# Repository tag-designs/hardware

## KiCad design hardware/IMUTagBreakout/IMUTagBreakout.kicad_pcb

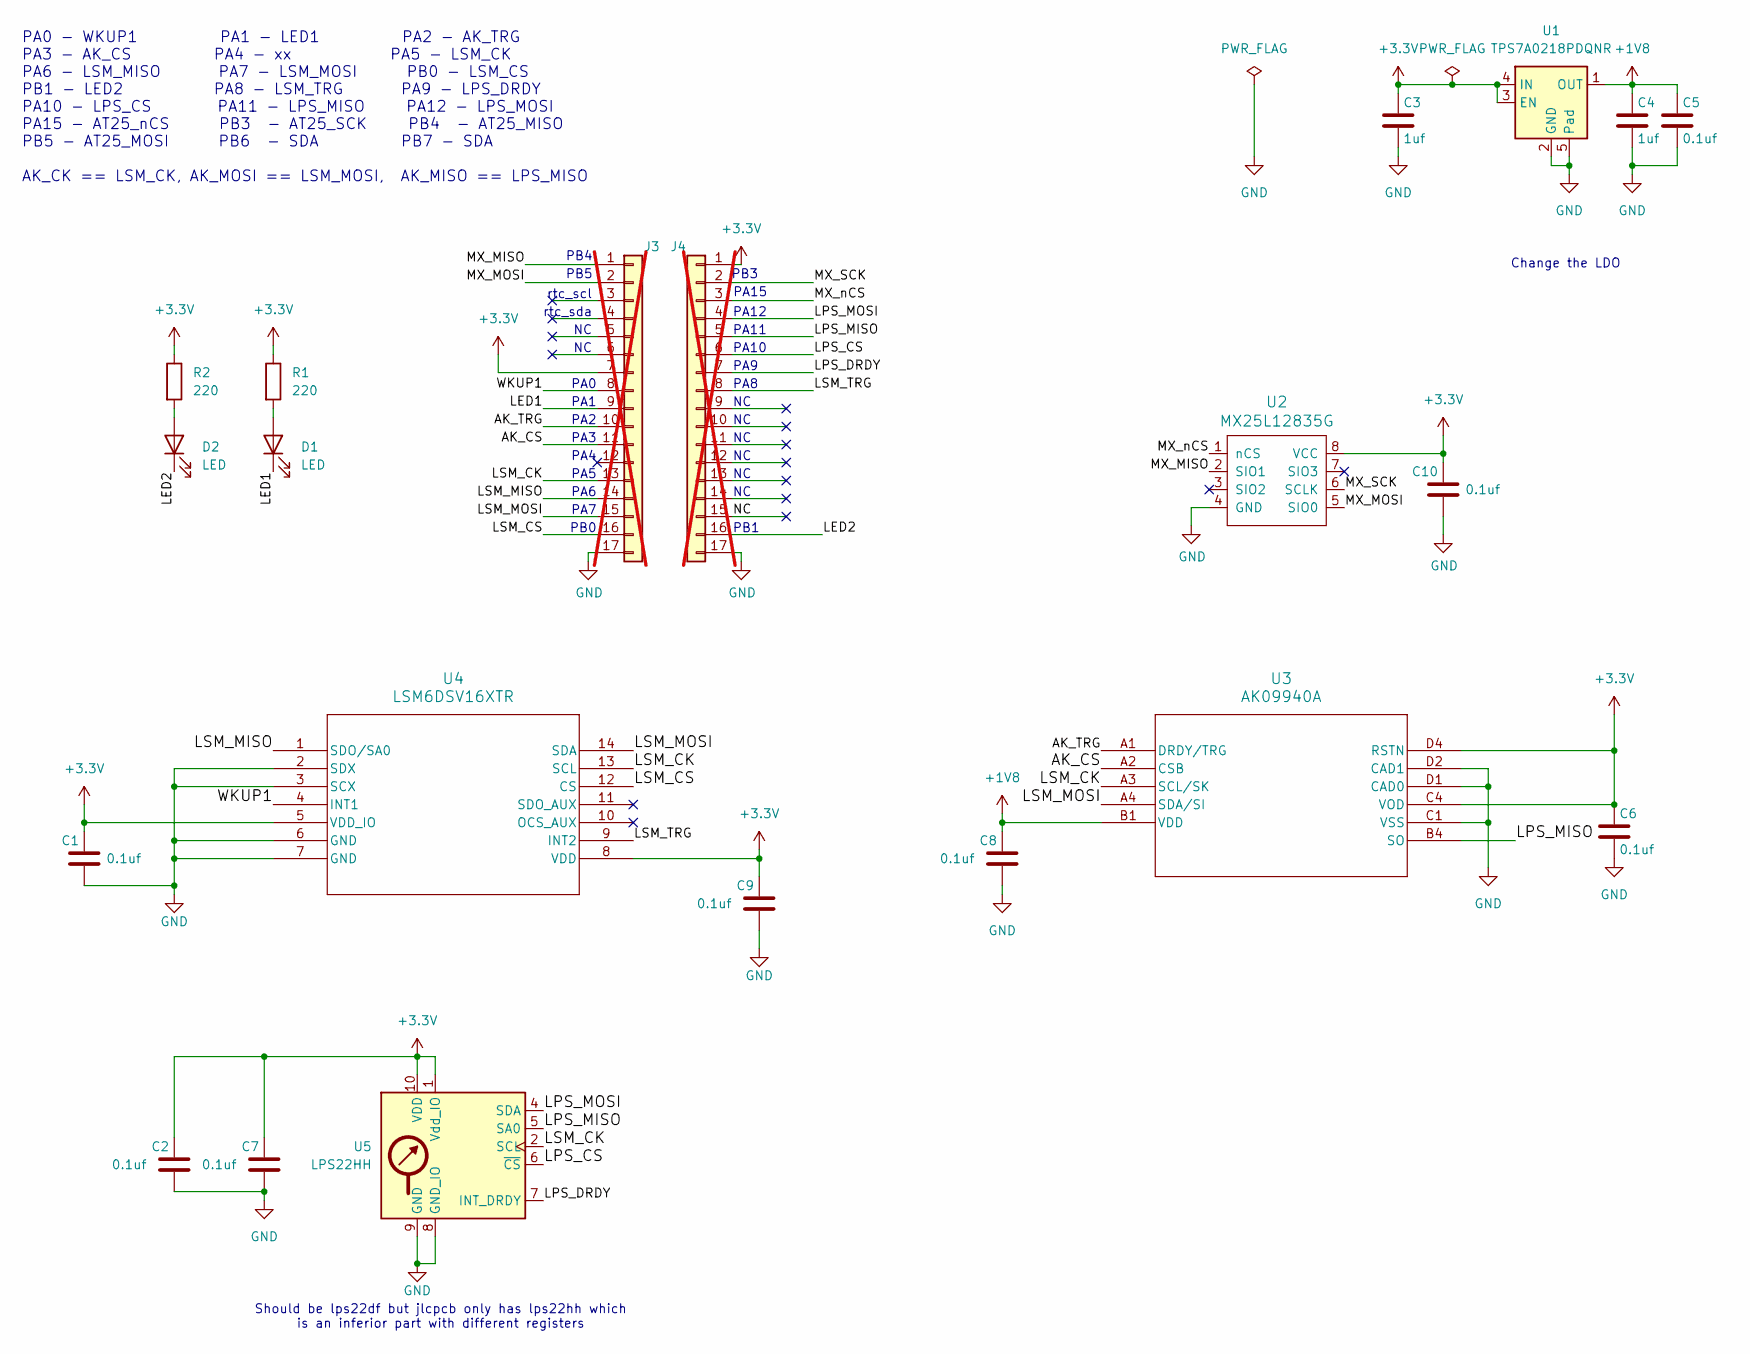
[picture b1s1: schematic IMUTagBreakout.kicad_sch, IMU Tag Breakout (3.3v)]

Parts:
C1, C2, C5, C6, C7, C8, C9, C10: 0.1uf; C_0603_1608Metric; MPN CC0603KRX7R9BB104; LCSC C14663
C3, C4: 1uf; C_0603_1608Metric; MPN CL10A105KB8NNNC; LCSC C15849
D1, D2: LED; LED_0603_1608Metric; MPN KT-0603R; LCSC C2286
J3, J4: Conn_01x17; PinHeader_1x17_P2.54mm_Vertical_Staggered; not fitted
R1, R2: 220; R_0603_1608Metric; MPN 0603WAF2200T5E; LCSC C22962
U1: TPS7A0218PDQNR; Texas_X2SON-4_1x1mm_P0.65mm; MPN TPS7A0218PDQNR; LCSC C2862166
U2: MX25L12835G; SOIC-8_5.3x6.2mm_P1.27mm; MPN MX25L12845GM2I-08G-TR; LCSC C136615
U3: AK09940A; AK09940a; MPN AK09940A; LCSC C6794828
U4: LSM6DSV16XTR; LGA-14_3x2.5mm_P0.5mm_LayoutBorder3x4y; MPN LSM6DSV; LCSC C5267406
U5: LPS22HH; ST_HLGA-10_2x2mm_P0.5mm_LayoutBorder3x2y; MPN LPS22HH; LCSC C2827824

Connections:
+1V8: C4.1, C5.1, C8.1, U1.1 (OUT), U3.B1 (VDD)
+3.3V: C1.1, C2.1, C3.1, C6.1, C7.1, C9.1, C10.1, J3.7, J4.1, R1.1, R2.1, U1.3 (EN), U1.4 (IN), U2.8 (VCC), U3.C4 (VOD), U3.D4 (RSTN), U4.5 (VDD_IO), U4.8 (VDD), U5.1 (Vdd_IO), U5.10 (VDD)
/AK_CS: J3.11, U3.A2 (CSB)
/AK_TRG: J3.10, U3.A1 (DRDY/TRG)
/LED1: D1.1 (K), J3.9
/LED2: D2.1 (K), J4.16
/LPS_CS: J4.6, U5.6 (~CS)
/LPS_DRDY: J4.7, U5.7 (INT_DRDY)
/LPS_MISO: J4.5, U3.B4 (SO), U5.5 (SA0)
/LPS_MOSI: J4.4, U5.4 (SDA)
/LSM_CK: J3.13, U3.A3 (SCL/SK), U4.13 (SCL), U5.2 (SCL)
/LSM_CS: J3.16, U4.12 (CS)
/LSM_MISO: J3.14, U4.1 (SDO/SA0)
/LSM_MOSI: J3.15, U3.A4 (SDA/SI), U4.14 (SDA)
/LSM_TRG: J4.8, U4.9 (INT2)
/MX_MISO: J3.1, U2.2 (SIO1)
/MX_MOSI: J3.2, U2.5 (SIO0)
/MX_SCK: J4.2, U2.6 (SCLK)
/MX_nCS: J4.3, U2.1 (nCS)
/NC: J4.15
/WKUP1: J3.8, U4.4 (INT1)
GND: C1.2, C2.2, C3.2, C4.2, C5.2, C6.2, C7.2, C8.2, C9.2, C10.2, J3.17, J4.17, U1.2 (GND), U1.5 (Pad), U2.4 (GND), U3.C1 (VSS), U3.D1 (CAD0), U3.D2 (CAD1), U4.2 (SDX), U4.3 (SCX), U4.6 (GND), U4.7 (GND), U5.3 (GND), U5.8 (GND_IO), U5.9 (GND)
unnamed: D1.2 (A), R1.2
unnamed: D2.2 (A), R2.2

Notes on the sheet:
PA1
PA9
PA2
PA0
PA8
PA7
PA15
PA5
PA4
PB3
PA6
Should be lps22df but jlcpcb only has lps22hh which is an inferior part with different registers
PA3
PB4
PA12
PB0
PA0 - WKUP1 PA1 - LED1 PA2 - AK_TRG PA3 - AK_CS PA4 - xx PA5 - LSM_CK PA6 - LSM_MISO PA7 - LSM_MOSI PB0 - LSM_CS PB1 - LED2 PA8 - LSM_TRG PA9 - LPS_DRDY PA10 - LPS_CS PA11 - LPS_MISO PA12 - LPS_MOSI PA15 - AT25_nCS PB3 - AT25_SCK PB4 - AT25_MISO PB5 - AT25_MOSI PB6 - SDA PB7 - SDA AK_CK == LSM_CK, 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
PB5
PA10
rtc_sda
PA11
PB1
rtc_scl
Change the LDO

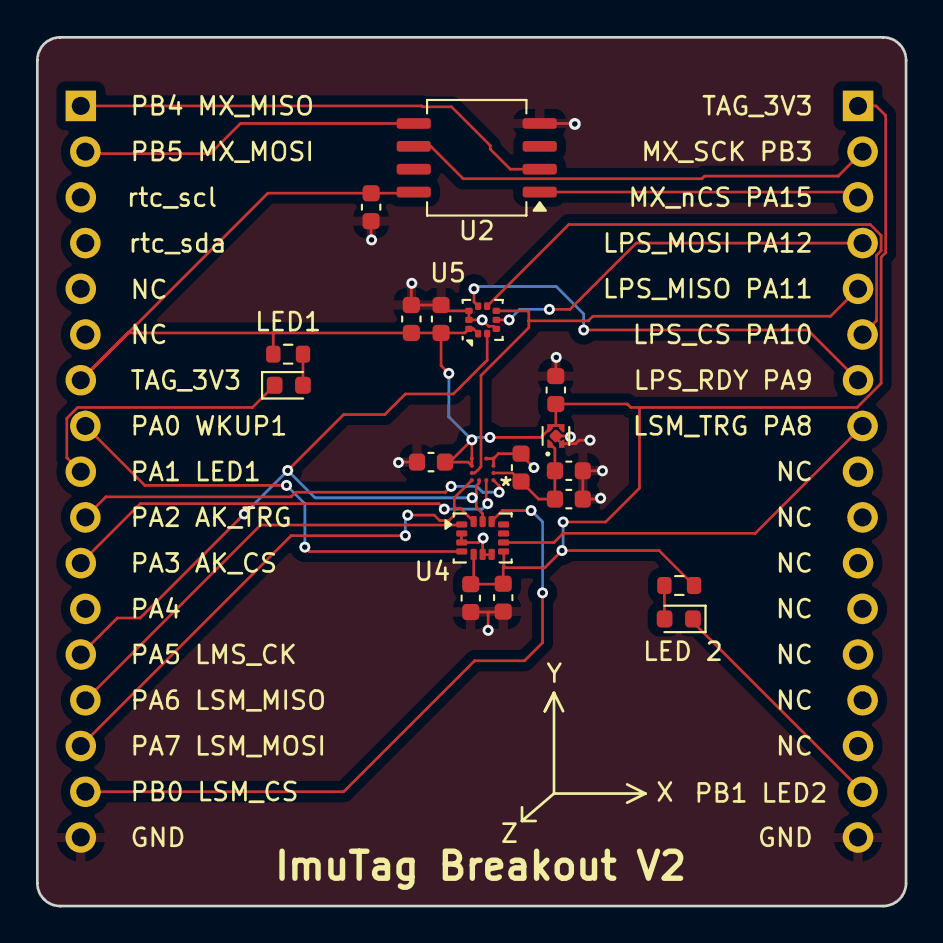
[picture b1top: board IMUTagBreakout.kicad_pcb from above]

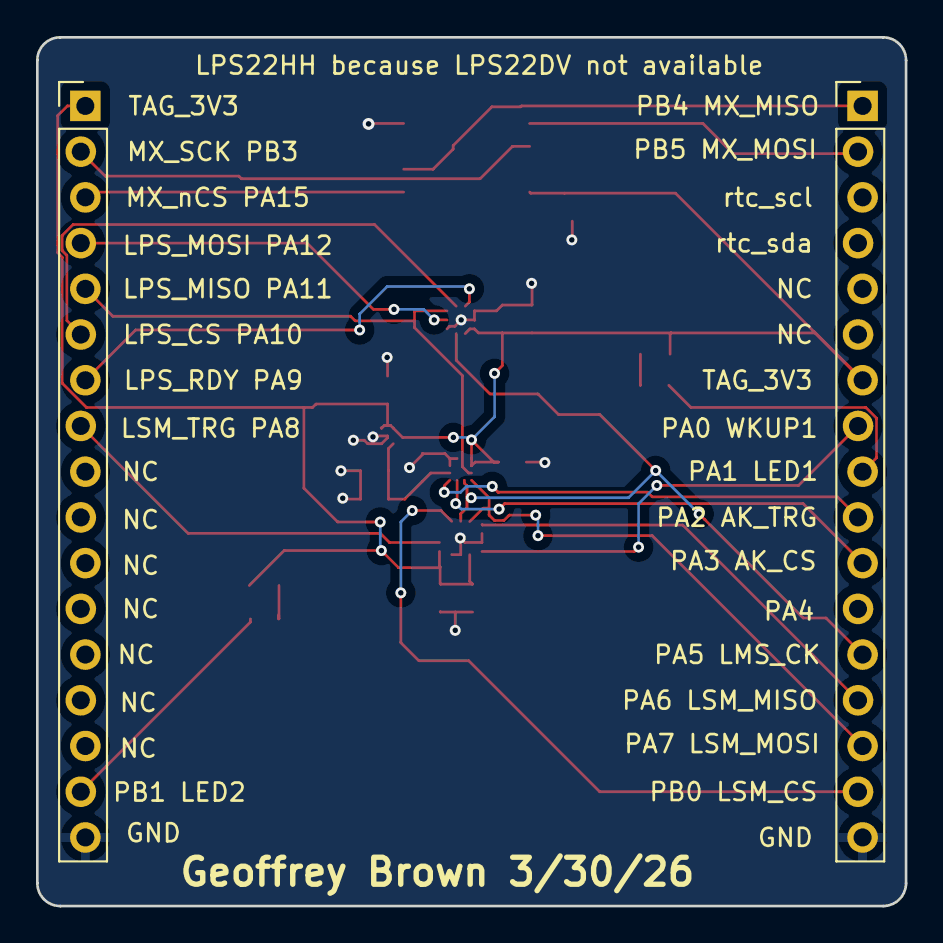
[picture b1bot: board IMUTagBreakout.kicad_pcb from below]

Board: 2 copper layers, 48.3 x 48.3 mm, 21 parts (2 on the bottom side), 23 nets.

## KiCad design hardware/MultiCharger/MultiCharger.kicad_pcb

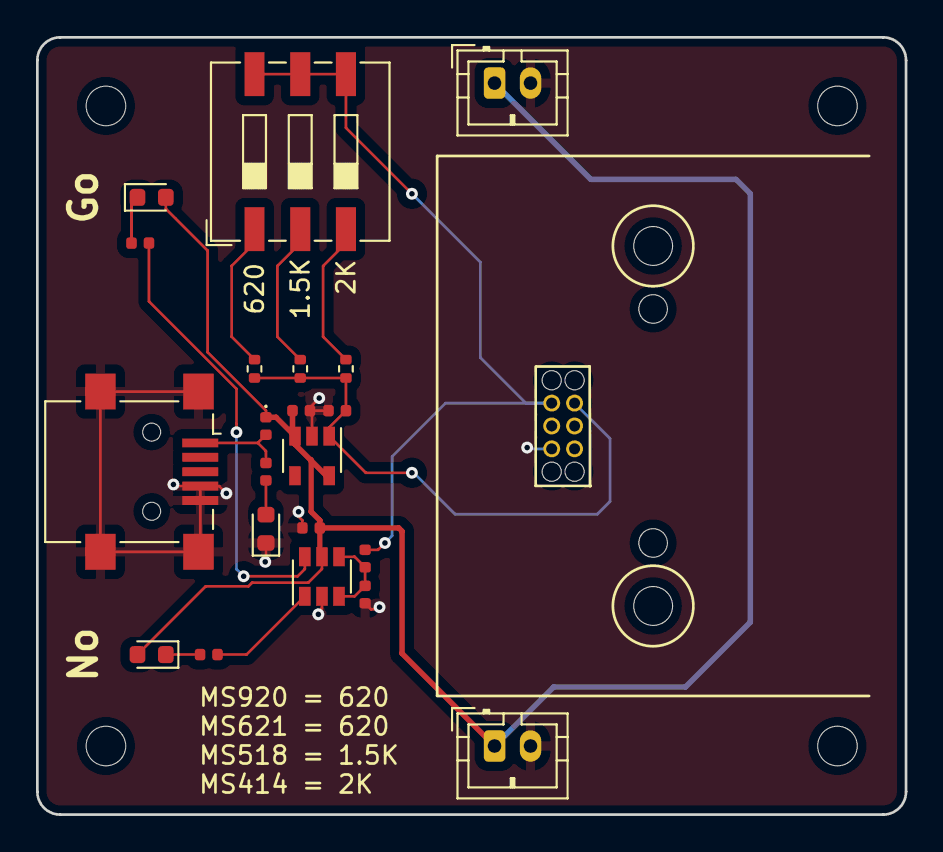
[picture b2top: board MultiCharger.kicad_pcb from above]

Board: 2 copper layers, 48.3 x 43.2 mm, 26 parts (0 on the bottom side), 14 nets.

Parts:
C101: 0.1uF; C_0402_1005Metric
C106: 1uF; C_0402_1005Metric
C107: 2.2uF; C_0402_1005Metric
D101: No Go; LED_0603_1608Metric
D102: LED; LED_0603_1608Metric
D103: Go; LED_0603_1608Metric
D104: D; D_0402_1005Metric
J101, J102: Conn_01x02; JST_PH_B2B-PH-K_1x02_P2.00mm_Vertical
J103: Tagbase; 6pin_tagpoints_new_offset
J104: USB_B_Mini; USB_Mini-B_Lumberg_2486_01_Horizontal
MK101, MK102, MK103, MK104: Mounting_Hole; MountingHole_2.2mm_M2
R1: 620; R_0402_1005Metric
R101, R102, R105: 1K; R_0402_1005Metric
R103: 910K; R_0402_1005Metric
R104: 130K; R_0402_1005Metric
R106: 1500; R_0402_1005Metric
R107: 2000; R_0402_1005Metric
SW101: SW_DIP_x03; SW_DIP_SPSTx03_Slide_9.78x9.8mm_W8.61mm_P2.54mm
U101: TLV6700; SOT-23-6
U106: TLV70A933_SOT23-5; SOT-23-5

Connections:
+3V3: C107.1, J103.5, R1.2, R106.2, R107.2, U106.1
/VIN: C101.1, C106.1, D101.2, D103.2, D104.1, J101.1, J102.1, U101.5, U106.3, U106.5
/Vsense: R103.2, R104.1, U101.3, U101.4
GND: C101.2, C106.2, C107.2, D102.1, J101.2, J102.2, J103.2, J104.4, J104.5, J104.6, R104.2, U101.2, U106.2
unnamed: D101.1, R101.2
unnamed: D102.2, R102.2
unnamed: D103.1, R105.2
unnamed: D104.2, J104.1, R102.1
unnamed: R1.1, SW101.1
unnamed: R101.1, U101.1
unnamed: R105.1, U101.6
unnamed: R106.1, SW101.2
unnamed: R107.1, SW101.3
TAG_VBAT: J103.6, R103.1, SW101.4, SW101.5, SW101.6

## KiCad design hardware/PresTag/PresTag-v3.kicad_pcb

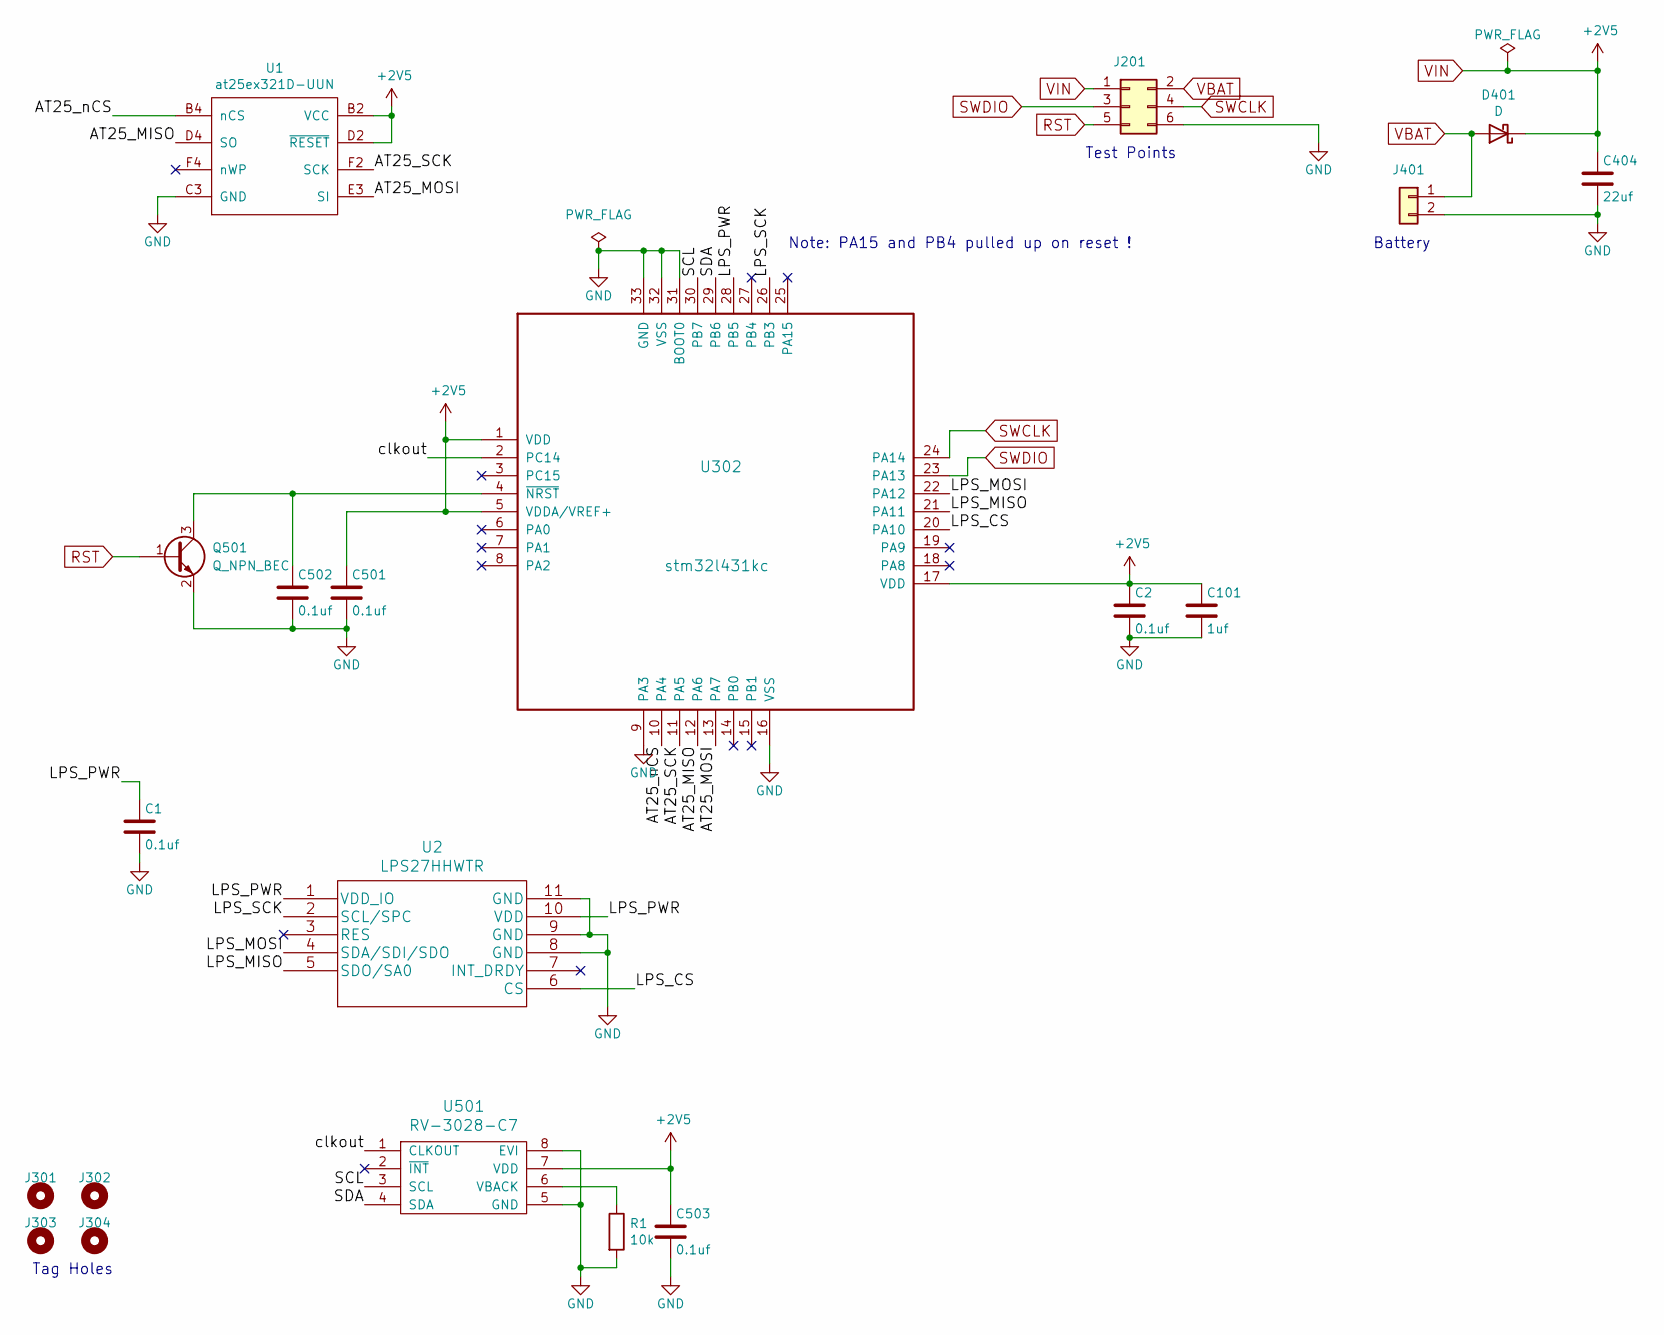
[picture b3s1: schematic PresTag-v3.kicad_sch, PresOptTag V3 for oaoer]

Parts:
C1, C2, C501, C502, C503: 0.1uf; C_0201_0603Metric; MPN GRM033C81E104KE14D
C101: 1uf; C_0201_0603Metric; MPN GRM033R60J105MEA2D
C404: 22uf; C_0402_1005Metric; MPN 04026D226MAT2A
D401: D; D_0402_1005Metric; MPN CDBQC0130L-HF
J201: CONN_02X04; tagpoints6
J301, J302, J303, J304: Conn_01x01; taghole1.1mm
J401: CONN_01X02; MS621
Q501: Q_NPN_BEC; SOT-883; MPN BC847AMB,315
R1: 10k; R_0201_0603Metric; MPN RC0201FR-0710KL
U1: at25ex321D-UUN; adesto_wlcsp12; MPN AT25XE321D-UUN-T
U2: LPS27HHWTR; MPN LPS27HHWTR
U302: stm32l431kc; QFN-32-1EP_5x5mm_P0.5mm_EP3.45x3.45mm; MPN STM32L431KCU6
U501: RV-3028-C7; RV-8803-C7; MPN RV-3028-C7 32.768KHZ 1PPM-TA-QC

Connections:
/AT25_MISO: U1.D4 (SO), U302.12 (PA6)
/AT25_MOSI: U1.E3 (SI), U302.13 (PA7)
/AT25_SCK: U1.F2 (SCK), U302.11 (PA5)
/AT25_nCS: U1.B4 (nCS), U302.10 (PA4)
/LPS_CS: U2.6 (CS), U302.20 (PA10)
/LPS_MISO: U2.5 (SDO/SA0), U302.21 (PA11)
/LPS_MOSI: U2.4 (SDA/SDI/SDO), U302.22 (PA12)
/LPS_PWR: C1.1, U2.1 (VDD_IO), U2.10 (VDD), U302.28 (PB5)
/LPS_SCK: U2.2 (SCL/SPC), U302.26 (PB3)
/SCL: U302.30 (PB7), U501.3 (SCL)
/SDA: U302.29 (PB6), U501.4 (SDA)
/clkout: U302.2 (PC14), U501.1 (CLKOUT)
GND: C1.2, C2.2, C101.2, C404.2, C501.2, C502.2, C503.2, J201.6, J401.2, Q501.2 (E), R1.2, U1.C3 (GND), U2.8 (GND), U2.9 (GND), U2.11 (GND), U302.9 (PA3), U302.16 (VSS), U302.31 (BOOT0), U302.32 (VSS), U302.33 (GND), U501.5 (GND), U501.8 (EVI)
unnamed: C502.1, Q501.3 (C), U302.4 (~NRST)
unnamed: R1.1, U501.6 (VBACK)
RST: J201.5, Q501.1 (B)
SWCLK: J201.4, U302.24 (PA14)
SWDIO: J201.3, U302.23 (PA13)
VBAT: D401.2 (A), J201.2, J401.1
VIN: C2.1, C101.1, C404.1, C501.1, C503.1, D401.1 (K), J201.1, U1.B2 (VCC), U1.D2 (~RESET), U302.1 (VDD), U302.5 (VDDA/VREF+), U302.17 (VDD), U501.7 (VDD)

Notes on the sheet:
Battery
Note: PA15 and PB4 pulled up on reset !
Tag Holes
Test Points

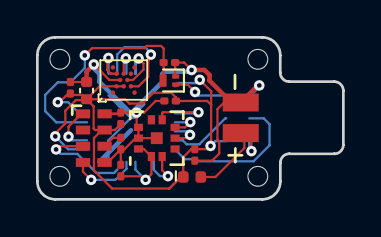
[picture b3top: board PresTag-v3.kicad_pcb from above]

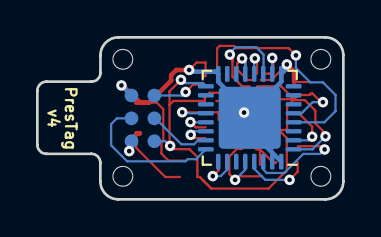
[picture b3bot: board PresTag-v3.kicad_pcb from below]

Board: 2 copper layers, 17.0 x 9.0 mm, 20 parts (2 on the bottom side), 20 nets.

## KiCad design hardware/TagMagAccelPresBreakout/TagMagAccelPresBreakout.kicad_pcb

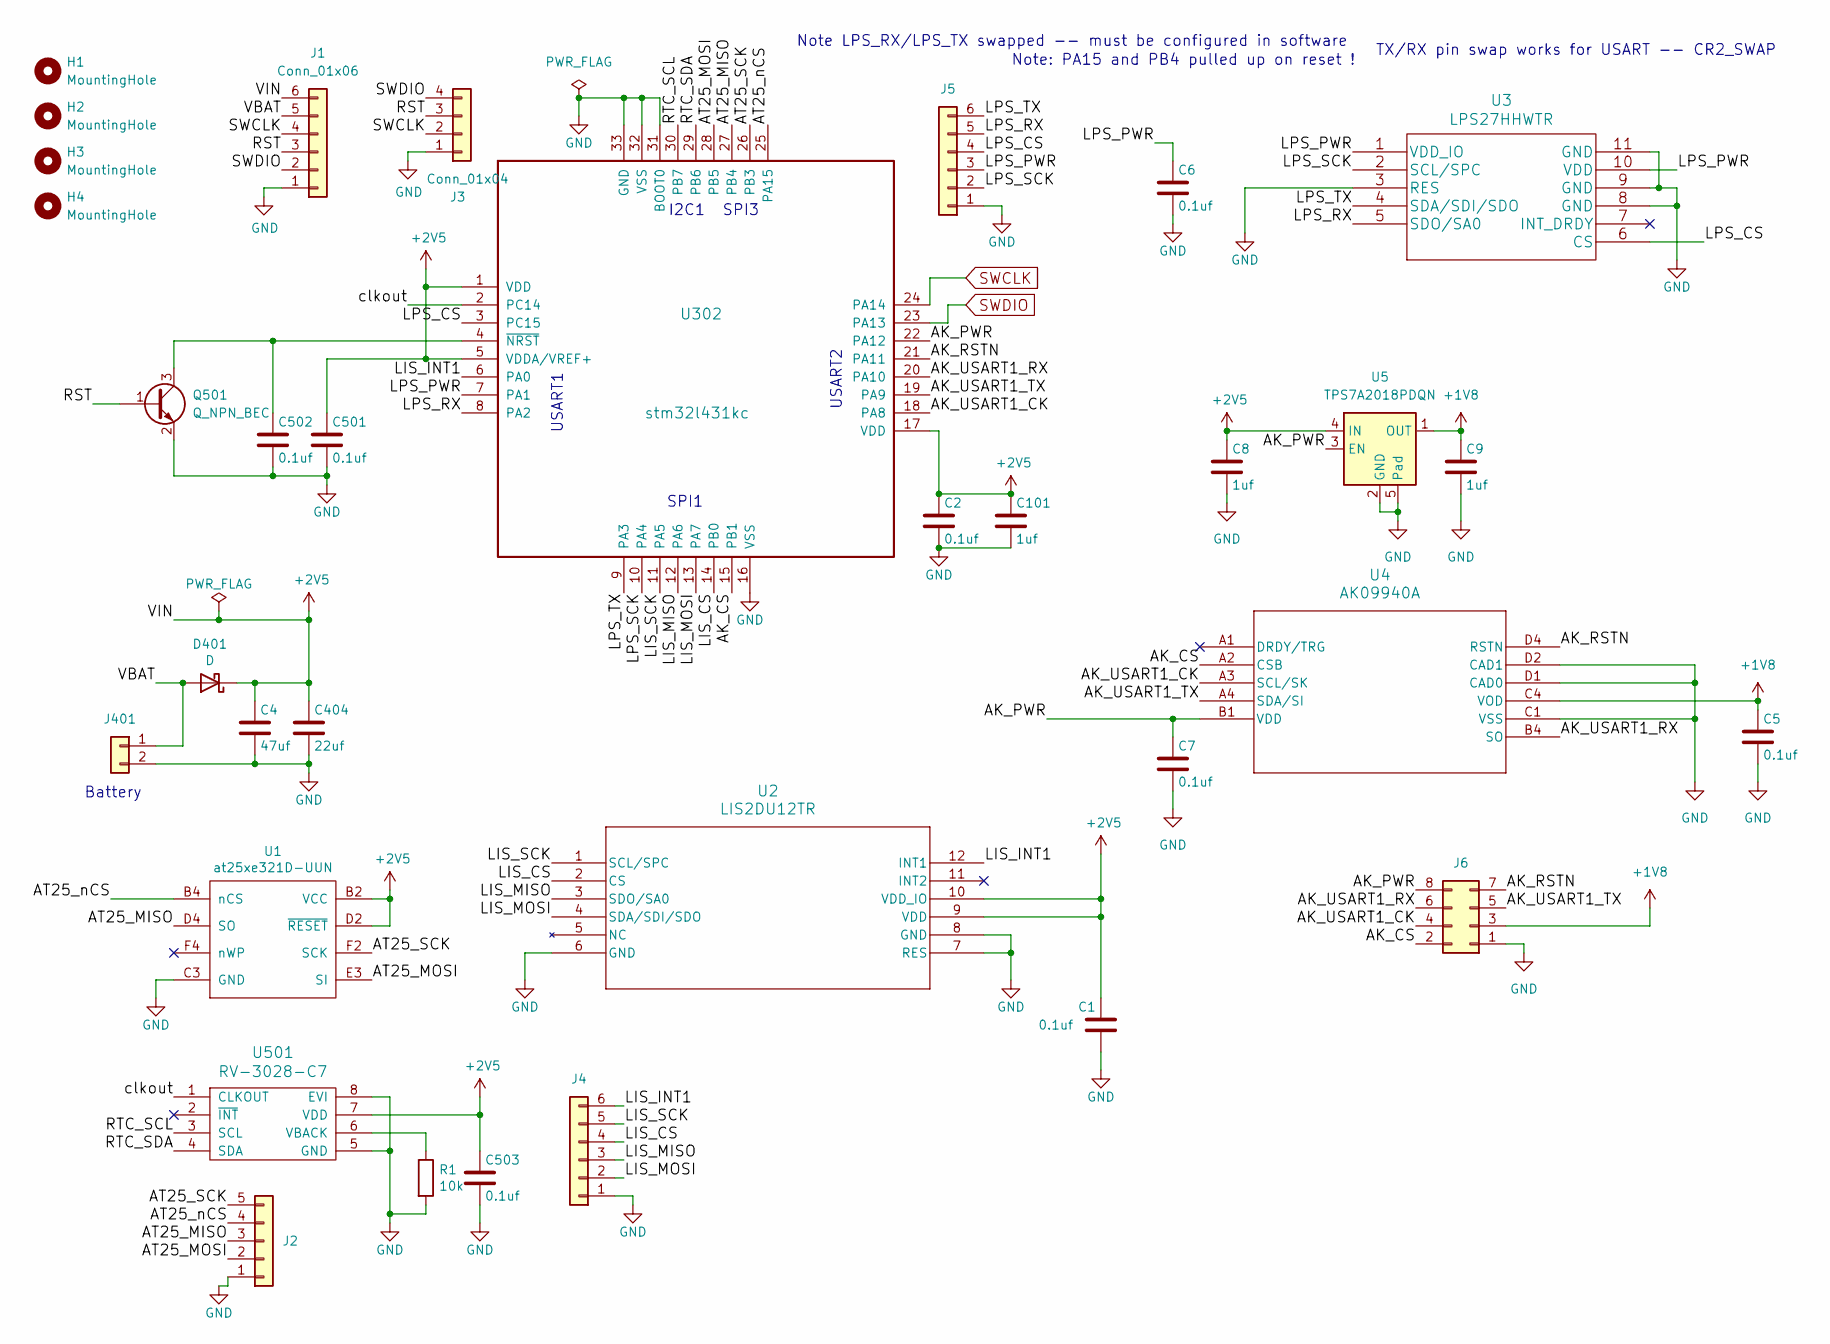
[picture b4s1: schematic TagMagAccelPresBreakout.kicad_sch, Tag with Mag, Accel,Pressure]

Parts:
C1: 0.1uf; C_0201_0603Metric; MPN GRM033C81E104KE14D; LCSC C181047
C2, C5, C6, C7, C501, C502, C503: 0.1uf; C_0201_0603Metric; MPN GRM033C81E104KE14D
C4: 47uf; C_0603_1608Metric; MPN 06036D476MAT2A
C8, C9, C101: 1uf; C_0201_0603Metric; MPN GRM033R60J105MEA2D
C404: 22uf; C_0402_1005Metric; MPN 04026D226MAT2A
D401: D; D_0402_1005Metric; MPN CDBQC0130L-HF
H1, H2, H3, H4: MountingHole; MountingHole_2.5mm
J1: Conn_01x06; CONN_B6B-ZR_JST
J2: Conn_01x04; PinHeader_1x05_P2.54mm_Vertical
J3: Conn_01x04; PinHeader_1x04_P2.54mm_Vertical
J4, J5: Conn_01x06; PinHeader_1x06_P2.54mm_Vertical
J6: Conn_02x04_Counter_Clockwise; PinHeader_2x04_P2.54mm_Vertical
J401: CONN_01X02; MS621
Q501: Q_NPN_BEC; SOT-883; MPN BC847AMB,315
R1: 10k; R_0201_0603Metric; MPN RC0201FR-0710KL
U1: at25xe321D-UUN; adesto_wlcsp12; MPN AT25XE321D-UUN-T
U2: LIS2DU12TR; LGA-12L_LIS2DU12_STM; MPN LIS2DU12TR
U3: LPS27HHWTR; MPN LPS27HHTWTR
U4: AK09940A; AK09940a; MPN AK09940A
U5: TPS7A2018PDQN; Texas_X2SON-4_1x1mm_P0.65mm; MPN TPS7A2018PDQNR
U302: stm32l431kc; QFN-32-1EP_5x5mm_P0.5mm_EP3.45x3.45mm; MPN STM32L431KCU6
U501: RV-3028-C7; RV-8803-C7; MPN RV-3028-C7 32.768KHZ 1PPM-TA-QC

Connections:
+1V8: C5.1, C9.1, J6.3, U4.C4 (VOD), U5.1 (OUT)
+2V5: C1.1, C2.1, C4.1, C8.1, C101.1, C404.1, C501.1, C503.1, D401.1 (K), J1.6, U1.B2 (VCC), U1.D2 (~RESET), U2.9 (VDD), U2.10 (VDD_IO), U5.4 (IN), U302.1 (VDD), U302.5 (VDDA/VREF+), U302.17 (VDD), U501.7 (VDD)
/AK_CS: J6.2, U4.A2 (CSB), U302.15 (PB1)
/AK_PWR: C7.1, J6.8, U4.B1 (VDD), U5.3 (EN), U302.22 (PA12)
/AK_RSTN: J6.7, U4.D4 (RSTN), U302.21 (PA11)
/AK_USART1_CK: J6.4, U4.A3 (SCL/SK), U302.18 (PA8)
/AK_USART1_RX: J6.6, U4.B4 (SO), U302.20 (PA10)
/AK_USART1_TX: J6.5, U4.A4 (SDA/SI), U302.19 (PA9)
/AT25_MISO: J2.3, U1.D4 (SO), U302.27 (PB4)
/AT25_MOSI: J2.2, U1.E3 (SI), U302.28 (PB5)
/AT25_SCK: J2.5, U1.F2 (SCK), U302.26 (PB3)
/AT25_nCS: J2.4, U1.B4 (nCS), U302.25 (PA15)
/LIS_CS: J4.4, U2.2 (CS), U302.14 (PB0)
/LIS_INT1: J4.6, U2.12 (INT1), U302.6 (PA0)
/LIS_MISO: J4.3, U2.3 (SDO/SA0), U302.12 (PA6)
/LIS_MOSI: J4.2, U2.4 (SDA/SDI/SDO), U302.13 (PA7)
/LIS_SCK: J4.5, U2.1 (SCL/SPC), U302.11 (PA5)
/LPS_CS: J5.4, U3.6 (CS), U302.3 (PC15)
/LPS_PWR: C6.1, J5.3, U3.1 (VDD_IO), U3.10 (VDD), U302.7 (PA1)
/LPS_RX: J5.5, U3.5 (SDO/SA0), U302.8 (PA2)
/LPS_SCK: J5.2, U3.2 (SCL/SPC), U302.10 (PA4)
/LPS_TX: J5.6, U3.4 (SDA/SDI/SDO), U302.9 (PA3)
/RST: J1.3, J3.3, Q501.1 (B)
/RTC_SCL: U302.30 (PB7), U501.3 (SCL)
/RTC_SDA: U302.29 (PB6), U501.4 (SDA)
/VBAT: D401.2 (A), J1.5, J401.1
/clkout: U302.2 (PC14), U501.1 (CLKOUT)
GND: C1.2, C2.2, C4.2, C5.2, C6.2, C7.2, C8.2, C9.2, C101.2, C404.2, C501.2, C502.2, C503.2, J1.1, J2.1, J3.1, J4.1, J5.1, J6.1, J401.2, Q501.2 (E), R1.2, U1.C3 (GND), U2.6 (GND), U2.7 (RES), U2.8 (GND), U3.3 (RES), U3.8 (GND), U3.9 (GND), U3.11 (GND), U4.C1 (VSS), U4.D1 (CAD0), U4.D2 (CAD1), U5.2 (GND), U5.5 (Pad), U302.16 (VSS), U302.31 (BOOT0), U302.32 (VSS), U302.33 (GND), U501.5 (GND), U501.8 (EVI)
unnamed: C502.1, Q501.3 (C), U302.4 (~NRST)
unnamed: R1.1, U501.6 (VBACK)
SWCLK: J1.4, J3.2, U302.24 (PA14)
SWDIO: J1.2, J3.4, U302.23 (PA13)

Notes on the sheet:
TX/RX pin swap works for USART -- CR2_SWAP
Battery
SPI3
Note: PA15 and PB4 pulled up on reset !
I2C1
Note LPS_RX/LPS_TX swapped -- must be configured in software
USART2
SPI1
USART1

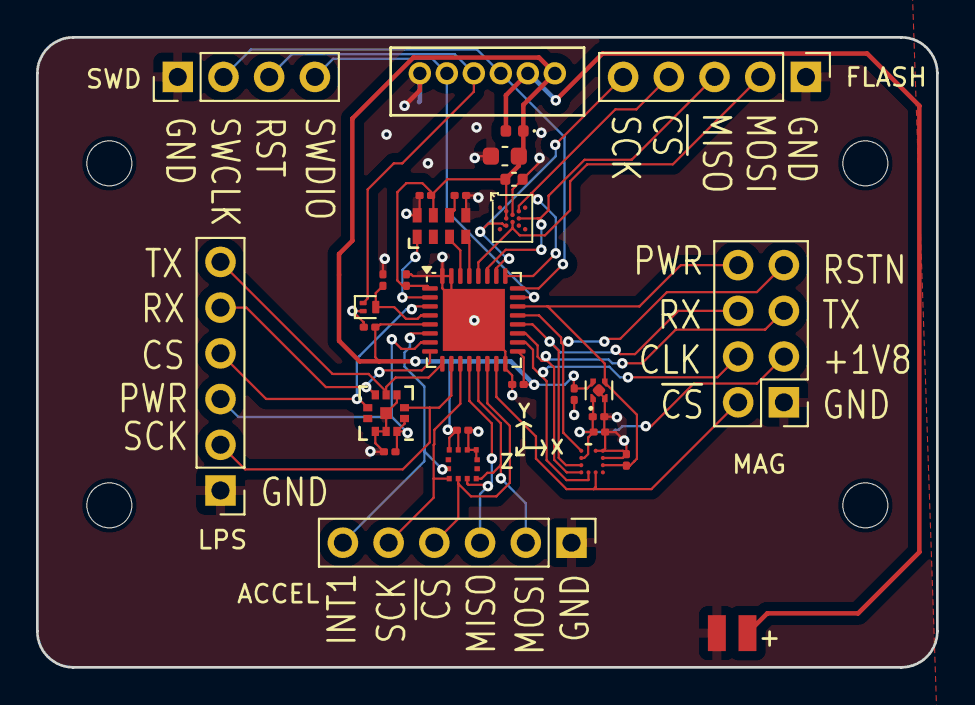
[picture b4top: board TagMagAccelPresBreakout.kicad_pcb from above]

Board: 2 copper layers, 50.0 x 35.0 mm, 34 parts (0 on the bottom side), 32 nets.

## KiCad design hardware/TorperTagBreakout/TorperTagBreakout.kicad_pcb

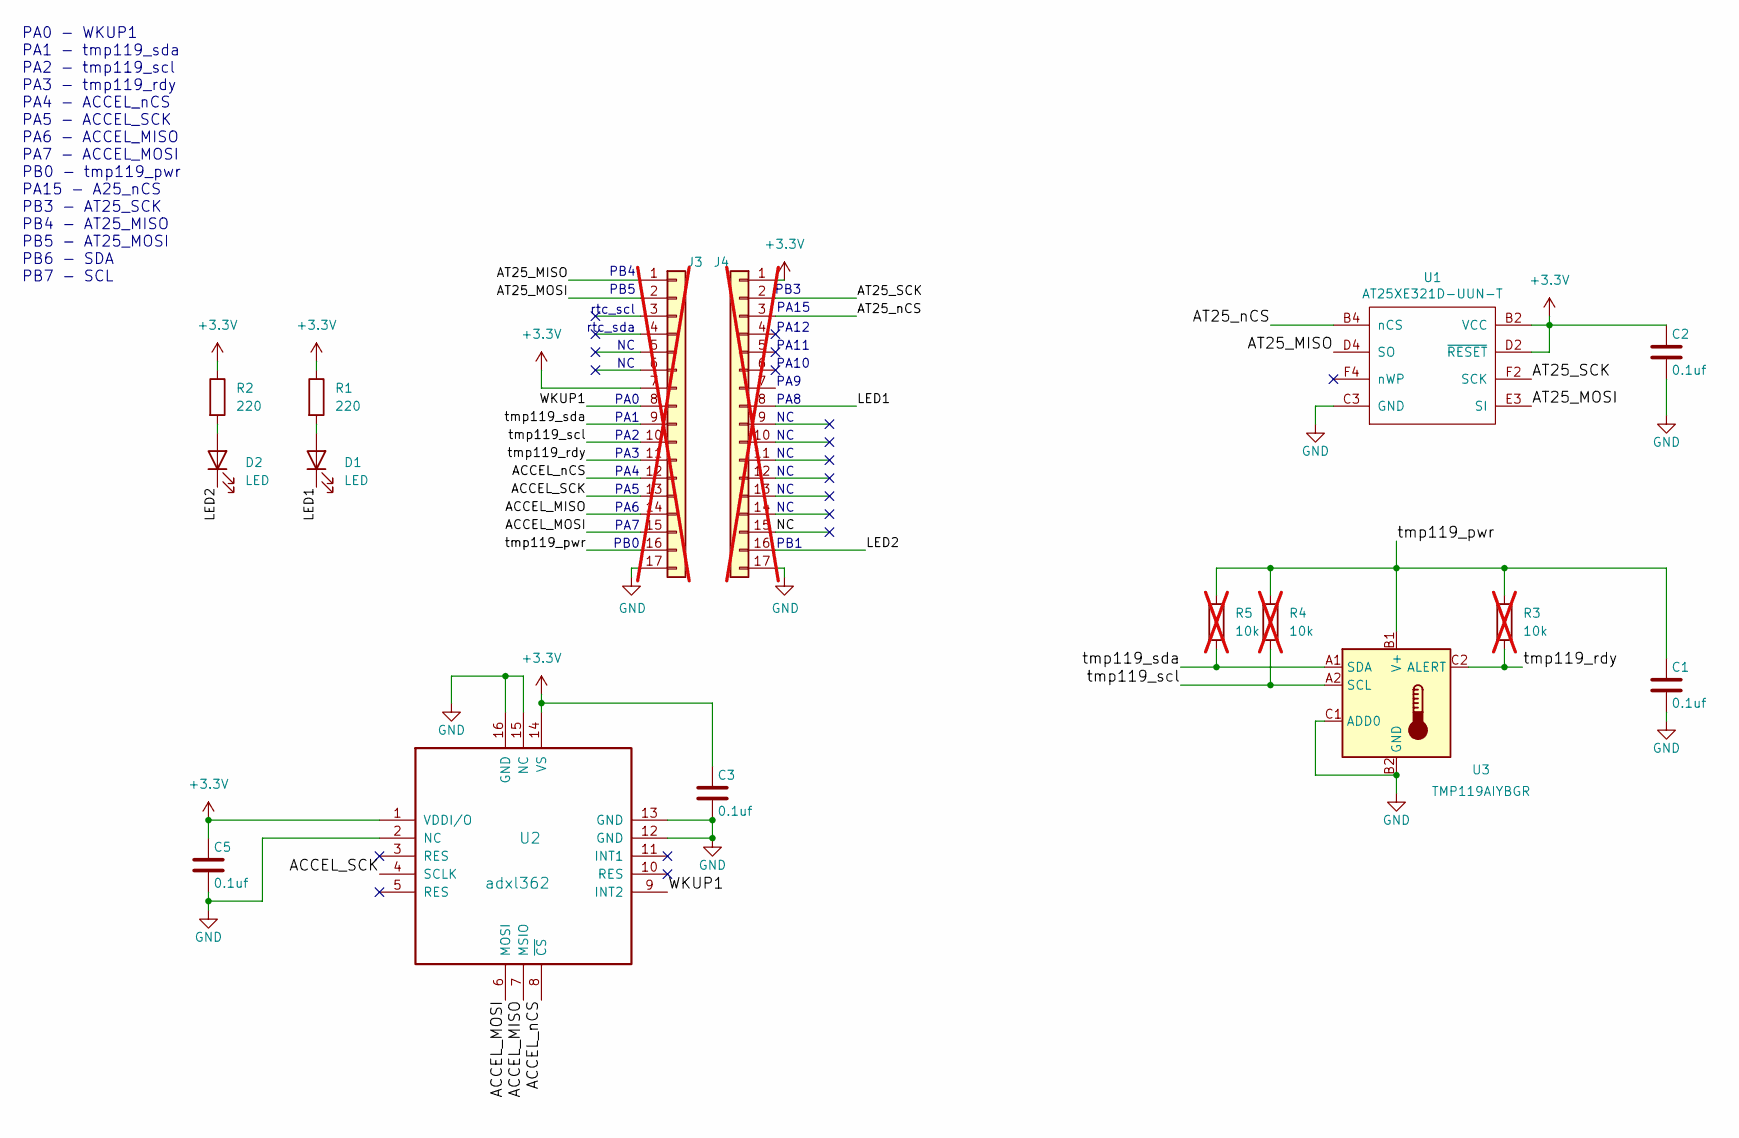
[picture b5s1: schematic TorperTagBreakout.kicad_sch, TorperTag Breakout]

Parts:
C1, C2, C3, C5: 0.1uf; C_0603_1608Metric; MPN CC0603KRX7R9BB104; LCSC C14663
D1, D2: LED; LED_0603_1608Metric; MPN KT-0603R; LCSC C2286
J3, J4: Conn_01x17; PinHeader_1x17_P2.54mm_Vertical_Staggered; not fitted
R1, R2: 220; R_0603_1608Metric; MPN 0603WAF2200T5E; LCSC C22962
R3, R4, R5: 10k; R_0805_2012Metric; MPN 0805W8F1002T5E; LCSC C17414; not fitted
U1: AT25XE321D-UUN-T; adesto_wlcsp12; MPN AT25XE321D-UUN-T; LCSC C1852767
U2: adxl362; ADXL362; MPN ADXL362BCCZ-RL7; LCSC C192252
U3: TMP119AIYBGR; Texas_DSBGA-6_0.95x1.488mm_Layout2x3_P0.4mm; MPN TMP119AIYBGR; LCSC C22428347

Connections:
+3.3V: C2.1, C3.1, C5.1, J3.7, J4.1, R1.1, R2.1, U1.B2 (VCC), U1.D2 (~RESET), U2.1 (VDDI/O), U2.14 (VS)
/ACCEL_MISO: J3.14, U2.7 (MSIO)
/ACCEL_MOSI: J3.15, U2.6 (MOSI)
/ACCEL_SCK: J3.13, U2.4 (SCLK)
/ACCEL_nCS: J3.12, U2.8 (~CS)
/AT25_MISO: J3.1, U1.D4 (SO)
/AT25_MOSI: J3.2, U1.E3 (SI)
/AT25_SCK: J4.2, U1.F2 (SCK)
/AT25_nCS: J4.3, U1.B4 (nCS)
/LED1: D1.1 (K), J4.8
/LED2: D2.1 (K), J4.16
/NC: J4.15
/WKUP1: J3.8, U2.9 (INT2)
/tmp119_pwr: C1.1, J3.16, R3.1, R4.1, R5.1, U3.B1 (V+)
/tmp119_rdy: J3.11, R3.2, U3.C2 (ALERT)
/tmp119_scl: J3.10, R4.2, U3.A2 (SCL)
/tmp119_sda: J3.9, R5.2, U3.A1 (SDA)
GND: C1.2, C2.2, C3.2, C5.2, J3.17, J4.17, U1.C3 (GND), U2.2 (NC), U2.12 (GND), U2.13 (GND), U2.15 (NC), U2.16 (GND), U3.B2 (GND), U3.C1 (ADD0)
unnamed: D1.2 (A), R1.2
unnamed: D2.2 (A), R2.2

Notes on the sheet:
PA1
PA9
PA2
PA0
PA8
PA7
PA15
PA5
PA4
PB3
PA6
PA0 - WKUP1 PA1 - tmp119_sda PA2 - tmp119_scl PA3 - tmp119_rdy PA4 - ACCEL_nCS PA5 - ACCEL_SCK PA6 - ACCEL_MISO PA7 - ACCEL_MOSI PB0 - tmp119_pwr PA15 - A25_nCS PB3 - AT25_SCK PB4 - AT25_MISO PB5 - AT25_MOSI PB6 - SDA PB7 - SCL
PA3
PB4
PA12
PB0
PB5
PA10
rtc_sda
PA11
PB1
rtc_scl

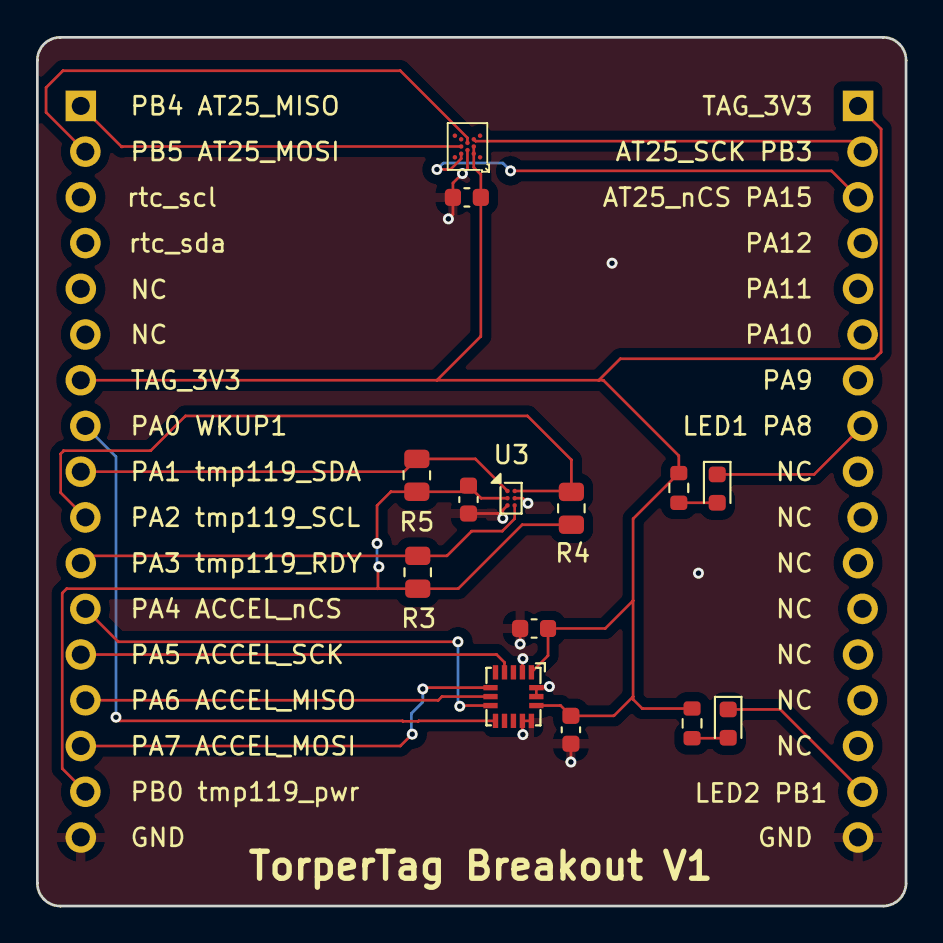
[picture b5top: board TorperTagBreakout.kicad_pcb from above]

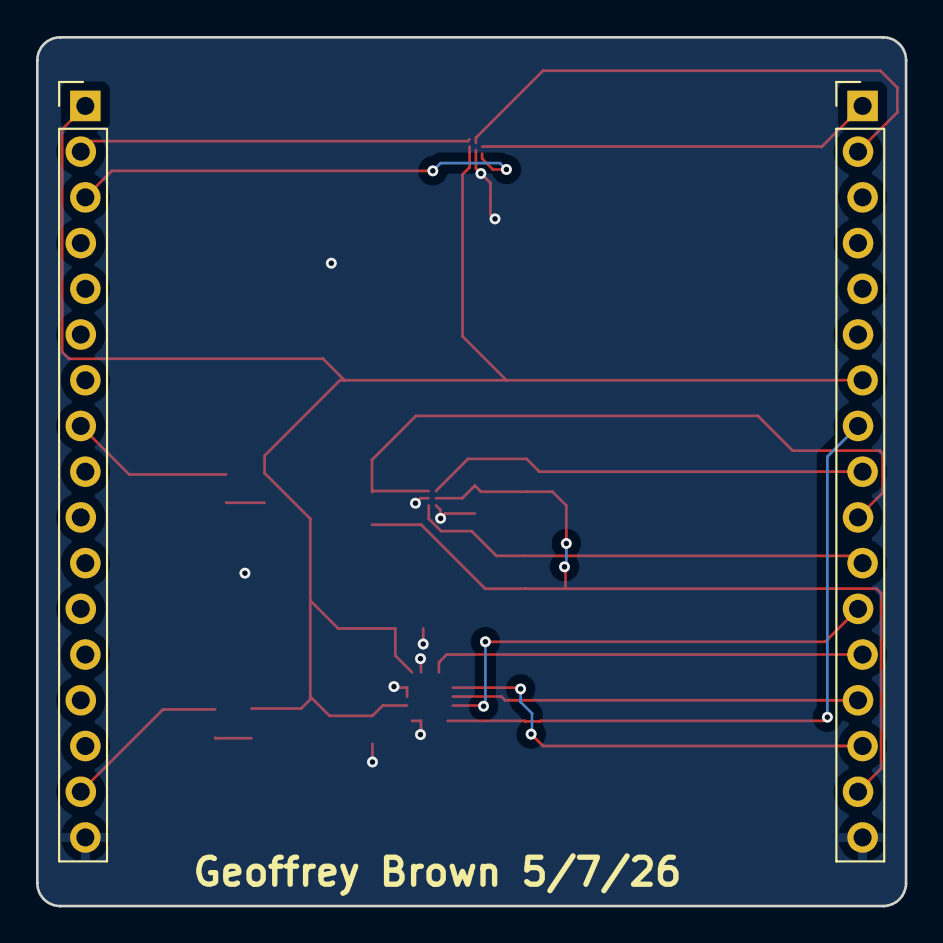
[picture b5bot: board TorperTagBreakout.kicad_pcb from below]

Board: 2 copper layers, 48.3 x 48.3 mm, 16 parts (2 on the bottom side), 19 nets.

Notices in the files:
parts and their libraries:
Copyright 2016 Accelerated Designs. All rights reserved.
